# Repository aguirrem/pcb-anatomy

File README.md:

# PCB Anatomy

**An agent skill for hardware: design boards in KiCad, review them, and draw them.**
Modelled on [Anatomy](https://github.com/wheresryan22/anatomy), whose isometric figure kit it builds on.

`examples/usb-blinky`, drawn from its own `.kicad_pcb`: every part at its package height, the +3V3 net lit with current flowing along it.

---

One skill, three modes:

| Mode | You ask for | You get |
|---|---|---|
| **Design** | "a USB-C powered ATtiny85 board, 32 × 24 mm, two layers, JLCPCB" | a KiCad 9/10 project built from one circuit spec: schematic (netlist parity and ERC clean), placed and autorouted board (DRC clean, ground stitched), renders, a self-review and fab outputs (Gerbers, drill, BOM, positions, IPC-2581, JLCPCB formats) |
| **Review** | "check this KiCad project before I order it" | a ranked report (blocker, major, minor, info) from ERC, DRC with schematic parity, fab limits, decoupling distances, floating inputs, current capacity, pair matching and BOM completeness, with every finding ringed on the board, plus the datasheet checks no script can do |
| **Illustrate** | "draw my board for the README" or "explain why decoupling caps sit by the pins" | an interactive isometric figure, from a real `.kicad_pcb` or an invented board built around the idea, in Anatomy's craft: solid parts, live readout from a true model, calm motion, checked in a headless browser |

## Quick start

```bash
git clone https://github.com/aguirrem/pcb-anatomy.git ~/.claude/skills/pcb-anatomy
bash ~/.claude/skills/pcb-anatomy/scripts/kicad/setup.sh      # KiCad 10, libraries, Java 25, Freerouting, headless Chrome
```

Then in Claude Code: `/pcb-anatomy design a breakout board for the BME280, I2C, 3.3 V, castellated edges`. In the Claude app, upload the folder as a skill (zip it with `SKILL.md` at the root). Claude also picks the skill up whenever you ask for anything PCB, schematic, KiCad, Gerber or hardware-figure shaped.

## Gallery

| | |
|---|---|
|  |  |
| **Space lifts the parts** off their pads on springs, so the copper under them shows. Monochrome "ink" palette. | **Review:** findings ringed and numbered on the board, matched to `review.md`. |
|  |  |
| **An idea figure:** slide C1 along the rails and the loop it closes with the chip's supply pins grows; the readout gives its inductance and its impedance at 100 MHz from `model.mjs`. | The same, dark theme, ink palette. |

## How it works

**Design** starts from a circuit spec (`spec.yaml`): parts as KiCad library symbols and footprints, nets as `REF.PIN` lists, deliberate no-connects, board size, rules, pours, and the placement of the parts that matter. `sch_build.py` writes the schematic and proves KiCad's netlist equals the spec; `pcb_build.py` builds the board from that netlist, places the anchors where the spec says and the passives next to what they serve (decoupling caps at supply pins); `route.py` routes with [Freerouting](https://github.com/freerouting/freerouting), refills pours and stitches ground; `outputs.py` writes fab files and refuses a board that fails DRC. `partgen.py` makes symbols and IPC-7351 footprints for parts KiCad lacks. Every step renders PNGs, and the skill tells Claude to look at them.

**Review** (`review.py`) works on any KiCad 8–10 project. The script does the measurable checks; `SKILL.md` and `references/review.md` give Claude the second pass: datasheets, reference circuits, protection, dissipation, manufacturability.

**Illustrate** extends Anatomy's kit (vendored, MIT, in `kit/anatomy/`) with `kit/pcb.mjs`: boards, copper, pads, vias, and packages built from footprint geometry (chips with tinned caps, gull-wing ICs with bent leads, QFNs, headers, USB-C shells, nylon housings, tactile switches, axial and disc parts, electrolytics, LEDs). `board_dump.py` reads a real board; `board-figure.mjs` makes the interactive page. Invented boards are built in millimetres with the same parts, driven by a pure model.

## Layout

```
pcb-anatomy/
├── SKILL.md                    what Claude reads: modes, workflow, rules
├── references/                 setup, spec format, design, parts, review, figures; anatomy/ (Anatomy's craft guides)
├── scripts/kicad/              setup.sh, find_part, sch_build, pcb_build, route, stitch, review, outputs,
│                               render, partgen, board_dump, and their helpers (sexp, spec, libsym, fplib, silk, kienv)
├── scripts/figure/             board-figure.mjs, and Anatomy's capture, drive and lines checks
├── kit/pcb.mjs                 PCB parts, palettes, boardFigure and its live script
├── kit/anatomy/                Anatomy's isometric kit, unchanged (MIT)
├── examples/usb-blinky/        a complete design: spec → schematic → board → review → fab → figure
├── examples/decoupling-loop/   an idea figure and its model
└── evals/evals.json            test prompts and what a good answer contains
```

## Requirements

KiCad 9 or 10 with `kicad-cli` and its Python module (design and review), Java 25 and Freerouting 2.5 (routing), Node.js 20.10+ and a headless Chrome (figures), PyYAML and librsvg. `scripts/kicad/setup.sh` installs or checks all of them on Linux and macOS and explains Windows; `references/setup.md` covers proxies, sandboxes and bundled-Python platforms.

## Limits

- **Autorouting is for simple and medium boards.** Route high-speed pairs, RF, crystals and switching-regulator loops by hand first; the skill says so and keeps your tracks with `--keep-tracks`.
- **Auto-placement only fills in.** Connectors, ICs and regulators are placed by intent in the spec.
- **The review is a second pair of eyes, not a sign-off.** Mains, high-current, RF, medical and safety-critical hardware need a qualified engineer.
- **Package heights in figures are guessed from footprint names** and can be corrected per part.

## License

MIT. The isometric kit in `kit/anatomy/`, the figure check scripts in `scripts/figure/` (except `board-figure.mjs` and `inline-kit.mjs`) and the guides in `references/anatomy/` come from [Anatomy](https://github.com/wheresryan22/anatomy) © 2026 Ryan, also MIT; see `kit/anatomy/LICENSE`. KiCad and Freerouting are installed separately under their own licences.

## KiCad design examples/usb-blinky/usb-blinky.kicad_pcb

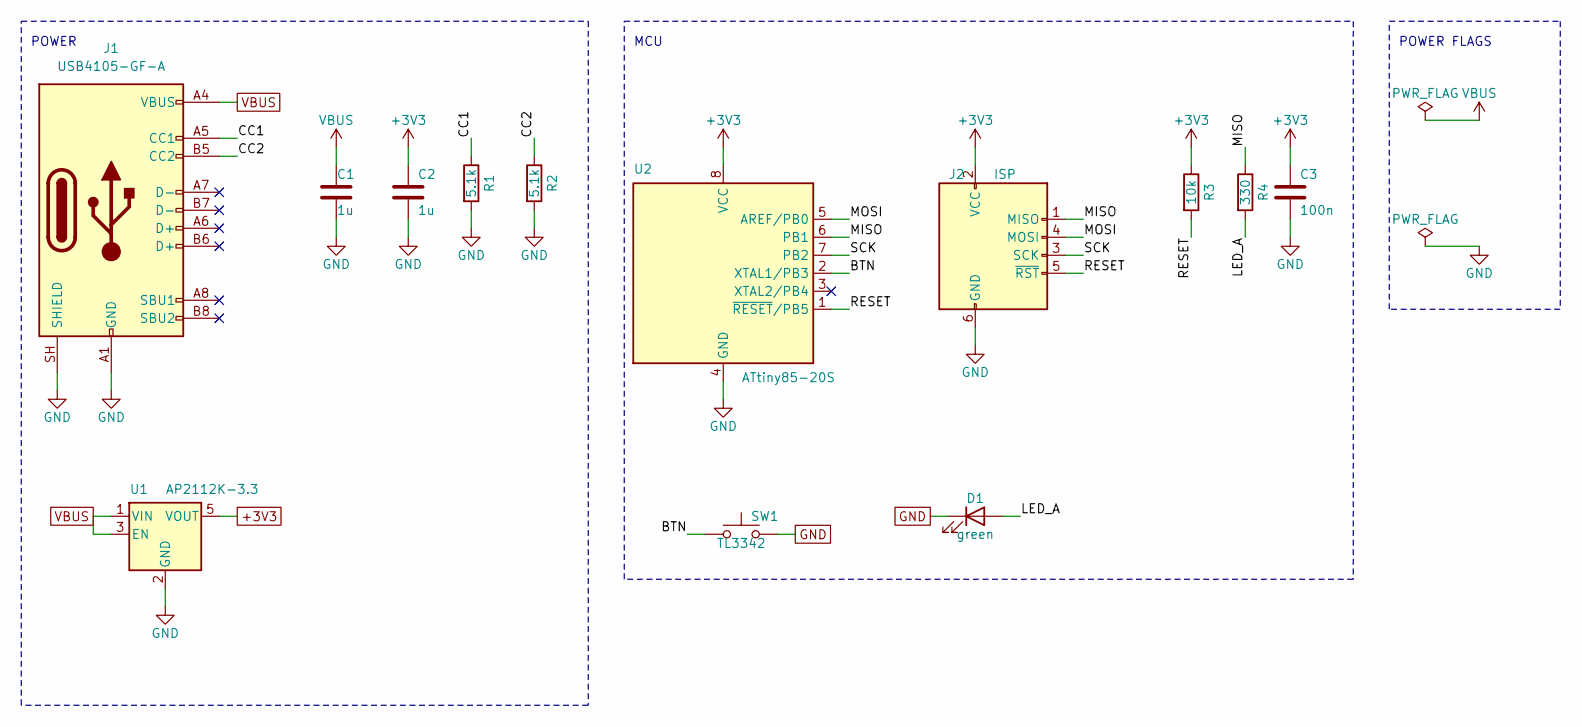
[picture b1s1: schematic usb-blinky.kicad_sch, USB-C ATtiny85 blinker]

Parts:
C1, C2: 1u; C_0603_1608Metric
C3: 100n; C_0603_1608Metric
D1: green; LED_0603_1608Metric
J1: USB4105-GF-A; USB_C_Receptacle_GCT_USB4105-xx-A_16P_TopMnt_Horizontal; MPN USB4105-GF-A
J2: ISP; PinHeader_2x03_P2.54mm_Vertical
R1, R2: 5.1k; R_0603_1608Metric
R3: 10k; R_0603_1608Metric
R4: 330; R_0603_1608Metric
SW1: TL3342; SW_SPST_TL3342
U1: AP2112K-3.3; SOT-23-5; MPN AP2112K-3.3TRG1
U2: ATtiny85-20S; SOIC-8_5.3x5.3mm_P1.27mm; MPN ATTINY85-20SU

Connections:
+3V3: C2.1, C3.1, J2.2 (VCC), R3.1, U1.5 (VOUT), U2.8 (VCC)
/BTN: SW1.1, U2.2 (XTAL1/PB3)
/CC1: J1.A5 (CC1), R1.1
/CC2: J1.B5 (CC2), R2.1
/LED_A: D1.2 (A), R4.2
/MISO: J2.1 (MISO), R4.1, U2.6 (PB1)
/MOSI: J2.4 (MOSI), U2.5 (AREF/PB0)
/RESET: J2.5 (~RST), R3.2, U2.1 (~RESET/PB5)
/SCK: J2.3 (SCK), U2.7 (PB2)
GND: C1.2, C2.2, C3.2, D1.1 (K), J1.A1 (GND), J1.A12 (GND), J1.B1 (GND), J1.B12 (GND), J1.SH (SHIELD), J2.6 (GND), R1.2, R2.2, SW1.2, U1.2 (GND), U2.4 (GND)
VBUS: C1.1, J1.A4 (VBUS), J1.A9 (VBUS), J1.B4 (VBUS), J1.B9 (VBUS), U1.1 (VIN), U1.3 (EN)

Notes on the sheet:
POWER
MCU
POWER FLAGS

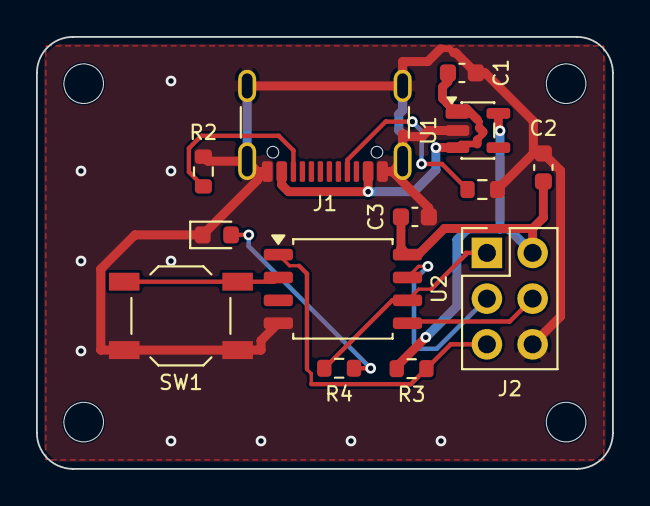
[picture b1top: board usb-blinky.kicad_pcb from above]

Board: 2 copper layers, 32.0 x 24.0 mm, 17 parts (0 on the bottom side), 11 nets.

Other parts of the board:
H1, H2, H3, H4: MountingHole; MountingHole_2.2mm_M2
